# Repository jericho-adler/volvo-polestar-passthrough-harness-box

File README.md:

# Volvo/Polestar Passthrough Harness Box

# 🚧 IN DEVELOPMENT 🚧

> [!WARNING]
> **This branch (`flexray-integration`) is work in progress and has not been built or tested in a vehicle.**
> The FlexRay schematic is complete and ERC-clean, and the PCB is fully routed and DRC-clean, but no board
> has been fabricated or bench-tested yet. The `main` branch holds the last stable design.

A small automotive ADAS harness pass-through box designed in KiCad, built for **Volvo/Polestar** vehicles. It sits inline on the camera/VCU harness and provides a fail-safe electrical bypass plus signal switching, protected against automotive power-rail transients and ESD.
- **Board:** 98.0 × 58.0 mm, 4-layer (F.Cu / In1.Cu=GND / In2.Cu / B.Cu), 80 components, 126 nets.
  Corners are radiused 3.8 mm, concentric with the four M3 mounting holes
- **Power inputs:** VBAT and VOBD, each TVS-protected (SMAJ16A) and OR'd through Schottky diodes (STPS2H100ZFY) into a combined VIN rail
- **Fail-safe passthrough:** a DPDT relay (Omron G5V-2-H1 DC12) wired so the normally-closed contacts connect CAMERA↔VCU when the box is unpowered, and open when VIN is applied. The coil sits directly across VIN/GND, so the high-sensitivity `-H1` variant is used: 150 mW instead of 500 mW, and a 180% max coil voltage (21.6 V) that tolerates a running alternator rail
- **Signal switching:** two DG419 SPDT analog switches route CAMERA/VCU signal pairs under control of an `SBU 1` logic input
- **Protection:** PESD1CAN ESD diodes on signal lines at the connectors
- **Connectors:** JAE MX34032NF4 (32-pin automotive, ×2) for the harness pass-through, plus a USB-C and Molex connector

## FlexRay MITM (this branch)

This branch adds a **man-in-the-middle tap on the vehicle's FlexRay bus** (harness pins 29 & 30) to the
existing pass-through box, so the bus can be observed and rewritten in transit rather than merely bridged.

The FlexRay pair no longer runs straight from `J4` (car harness) to `J3` (VCU module). It is cut into two
independent halves — `FR_VEH_P`/`FR_VEH_N` on `J4` and `FR_ECU_P`/`FR_ECU_N` on `J3` — each terminated in
its own transceiver, with the microcontroller between them relaying frames.

- **Controller:** Seeed **XIAO RP2350** module (`U4`), running [dynm/pico-flexray](https://github.com/dynm/pico-flexray)
- **Transceivers:** two **NXP TJA1082** (`U5` VCU module side on `J3`, `U6` car harness side on `J4`), one per bus half. Logic pins run
  to the XIAO as `FR1_*`/`FR2_*` (RXD/TXD/TXEN) with shared `FR_BGE` and `FR_STBN`; `VCC` on +5 V, `VIO` on
  +3.3 V so the module's own LDO sets the logic level
- **Fail-safe bypass:** a second DPDT relay `K2` (Omron G5V-2-H1 DC12) whose **normally-closed** contacts bridge
  the two halves back together. De-energized — unpowered box, crashed firmware, or the XIAO simply not driving
  it — the vehicle and ECU are wired directly to each other and the bus behaves as if the box were not there.
  Energizing it **splits** the bus into the MITM path. Driven from the XIAO via `FR_BYPASS_CTRL` → `Q2`
  (DMN3200U) with a 1N4148 flyback diode
- **Power:** `U3` **LM53601-Q1** buck (12 V → 5 V, always-on, forced PWM) with a 4.7 µH Coilcraft XAL4030
  inductor, feeding the XIAO's 5 V input; the XIAO's 3V3 regulator in turn supplies transceiver `VIO`
- **Protection:** PESD1FLEX ESD diodes (`D10`, `D11`) on each bus half at its connector

The original harness board — relay `K1` plus the two DG419 analog switches — is
**unchanged** and operates independently of the FlexRay circuit.

### Mechanical and DRC notes

- **Outline:** 98.0 × 58.0 mm. The four corners are arcs of **R3.8 mm** whose centres sit exactly on the
  mounting-hole centres, so each corner is concentric with its hole.
- **Mounting:** 4 × M3 holes, 3.2 mm drill, **non-plated**, inset 3.8 mm from both edges (`H1`–`H4`).
  They are deliberately non-plated so the enclosure screws do not bond chassis to board ground — harness
  pin 13 is not board GND. They exist on the PCB only, with no schematic symbols, so do not tick
  *delete footprints with no symbol* when running **Update PCB from Schematic**.
- **Edge-mounted connectors:** `J1`–`J4` overhang the board edge by design. `J3`/`J4` (JAE MX34032NF4)
  project 7.8 mm past the left and right edges respectively; their pads remain fully on the board.
- **Custom DRC rule** (`Polestar_Flexray.kicad_dru`): exempts intra-footprint pad spacing on `U3` and `U8`
  only. `U8`'s land pattern is based on TI drawing 4225320/A (RGY0020A), which places the exposed pad
  0.025 mm from every perimeter pin. On this board the 20 perimeter pads are **deliberately extended
  0.3 mm outward** beyond TI's pattern (extents about 3.9 × 4.9 mm instead of 3.3 × 4.3 mm), which opens that
  gap to 0.325 mm. The pads are non-solder-mask-defined, so bridging to the exposed pad is controlled by the
  stencil (78% paste coverage on pad 21) rather than by copper spacing. The rule is scoped to `U3`/`U8` so
  every other footprint is still checked normally.

### Status

| | |
|---|---|
| Schematic | Complete — 80 components, 0 ERC errors |
| Footprints & 3D models | All 80 components assigned and resolving |
| Placement | Complete — 84 footprints (80 components + 4 mounting holes) on a 98 × 58 mm outline |
| Routing | **Complete** — 1370 track segments, 224 vias, 0 unrouted. In1.Cu is a solid GND pour; In2.Cu is a +5V plane with a VIN island under the input and buck section; all pours filled |
| DRC | 0 errors, 0 unconnected, 0 silkscreen warnings. The only warnings left are 12 footprints that differ from `Library/` (board-local silkscreen trims) and 4 schematic-parity notes for the `H1`–`H4` mounting holes, which have no symbols |
| Firmware | In Progress with Dev Board |
| Bench / vehicle testing | In Progress with Dev Board |

### Libraries

Custom symbols and footprints live in [`Library/`](Library/), and [`PCB Files/`](PCB%20Files/) carries
project-local `fp-lib-table` and `sym-lib-table` pointing at them through `${KIPRJMOD}`. The project
therefore opens on a fresh clone without editing any global KiCad library table.

| | |
|---|---|
| `Library/Symbols/` | 6 symbol libraries — 17 custom symbols, all resolving |
| `Library/Footprints.pretty/` | 91 footprints — the 33 used by this design all resolve |

Everything else comes from stock KiCad libraries (`Device`, `power`, `Crystal`, `Inductor_SMD`,
`Package_SO`, `Package_SON`, `MountingHole`).

> [!NOTE]
> **3D models are not included.** 44 of the model references point at a personal model directory
> (`${KICAD_USER_3D_MODELS}`, 14 distinct files — the XIAO, both JAE connectors, Molex, TJA1082,
> DG419, TCAN4550 and others). Those parts will render as bare pads in the 3D viewer on a clone.
> The design, netlist, footprints and fabrication outputs are unaffected. The remaining 36 model
> references resolve from stock KiCad.

Project files live in [`PCB Files/`](PCB%20Files/) as `Polestar_Flexray.kicad_{pro,sch,pcb,dru}`.

> [!IMPORTANT]
> `Polestar_Flexray.kicad_dru` carries a custom DRC rule and should be kept beside the project files.
> The current board passes DRC without it, but restoring `U8` to TI's exact land pattern would bring back
> 20 false clearance errors. See **Mechanical and DRC notes** above.

## License

Licensed under the [CERN Open Hardware Licence Version 2 - Strongly Reciprocal](LICENSE) (CERN-OHL-S-2.0).

## Disclaimer

This is a community hardware design shared as-is, with no warranty. It is designed specifically for Volvo/Polestar vehicles — using it on other platforms is unverified. **Use at your own risk.** Review the design review's blockers before fabricating or installing in a vehicle.

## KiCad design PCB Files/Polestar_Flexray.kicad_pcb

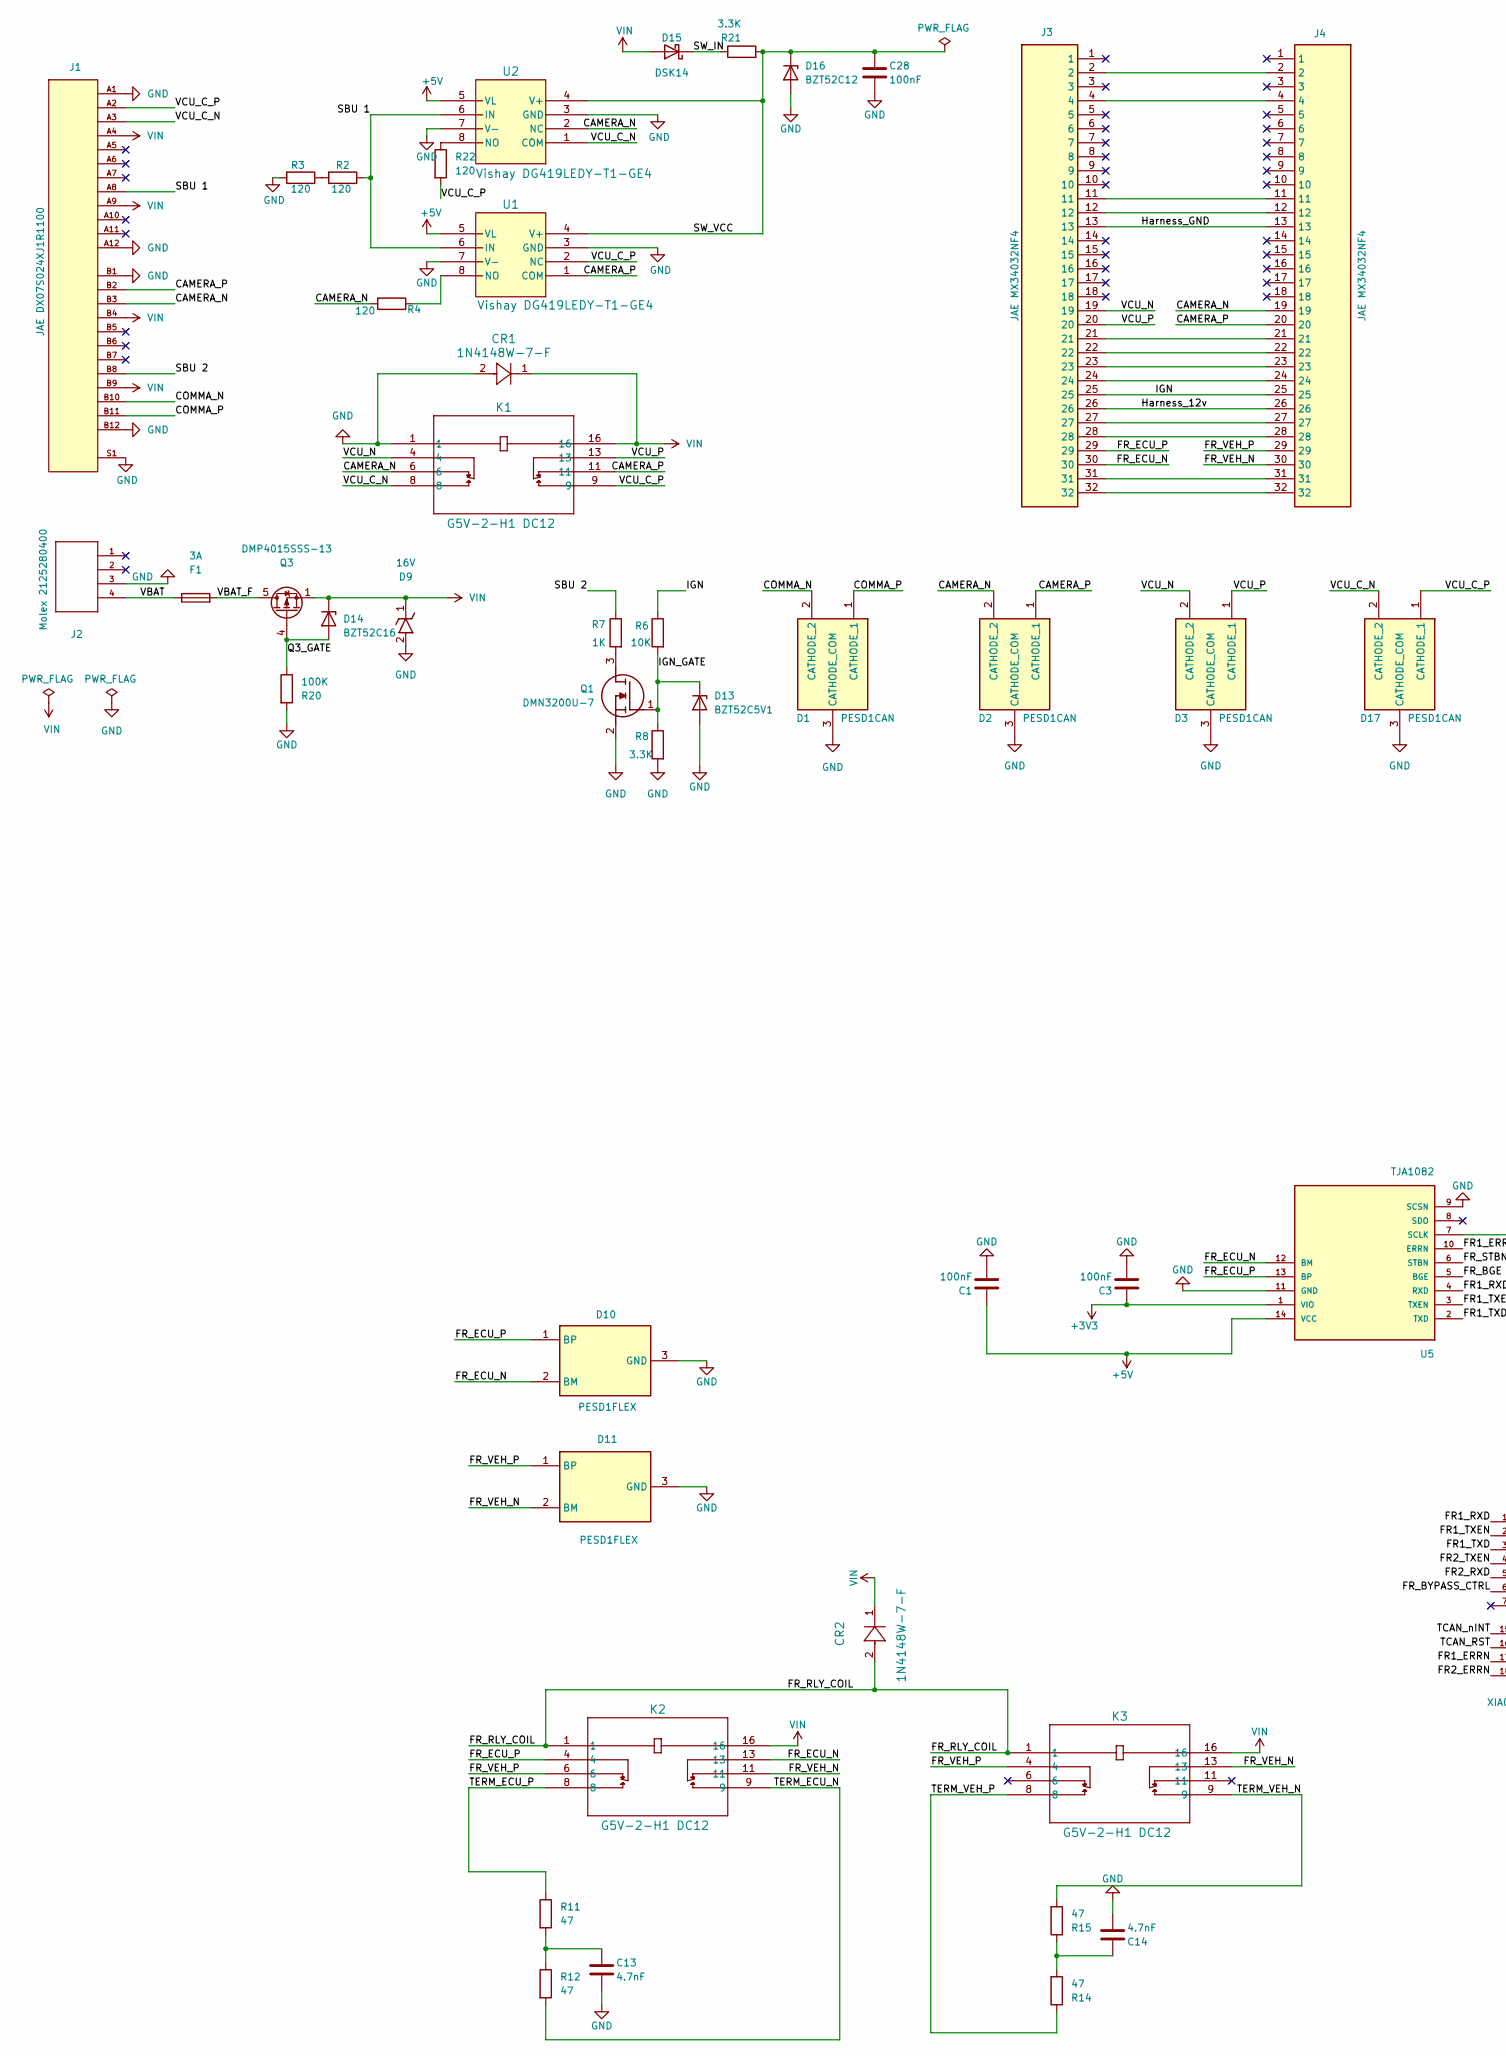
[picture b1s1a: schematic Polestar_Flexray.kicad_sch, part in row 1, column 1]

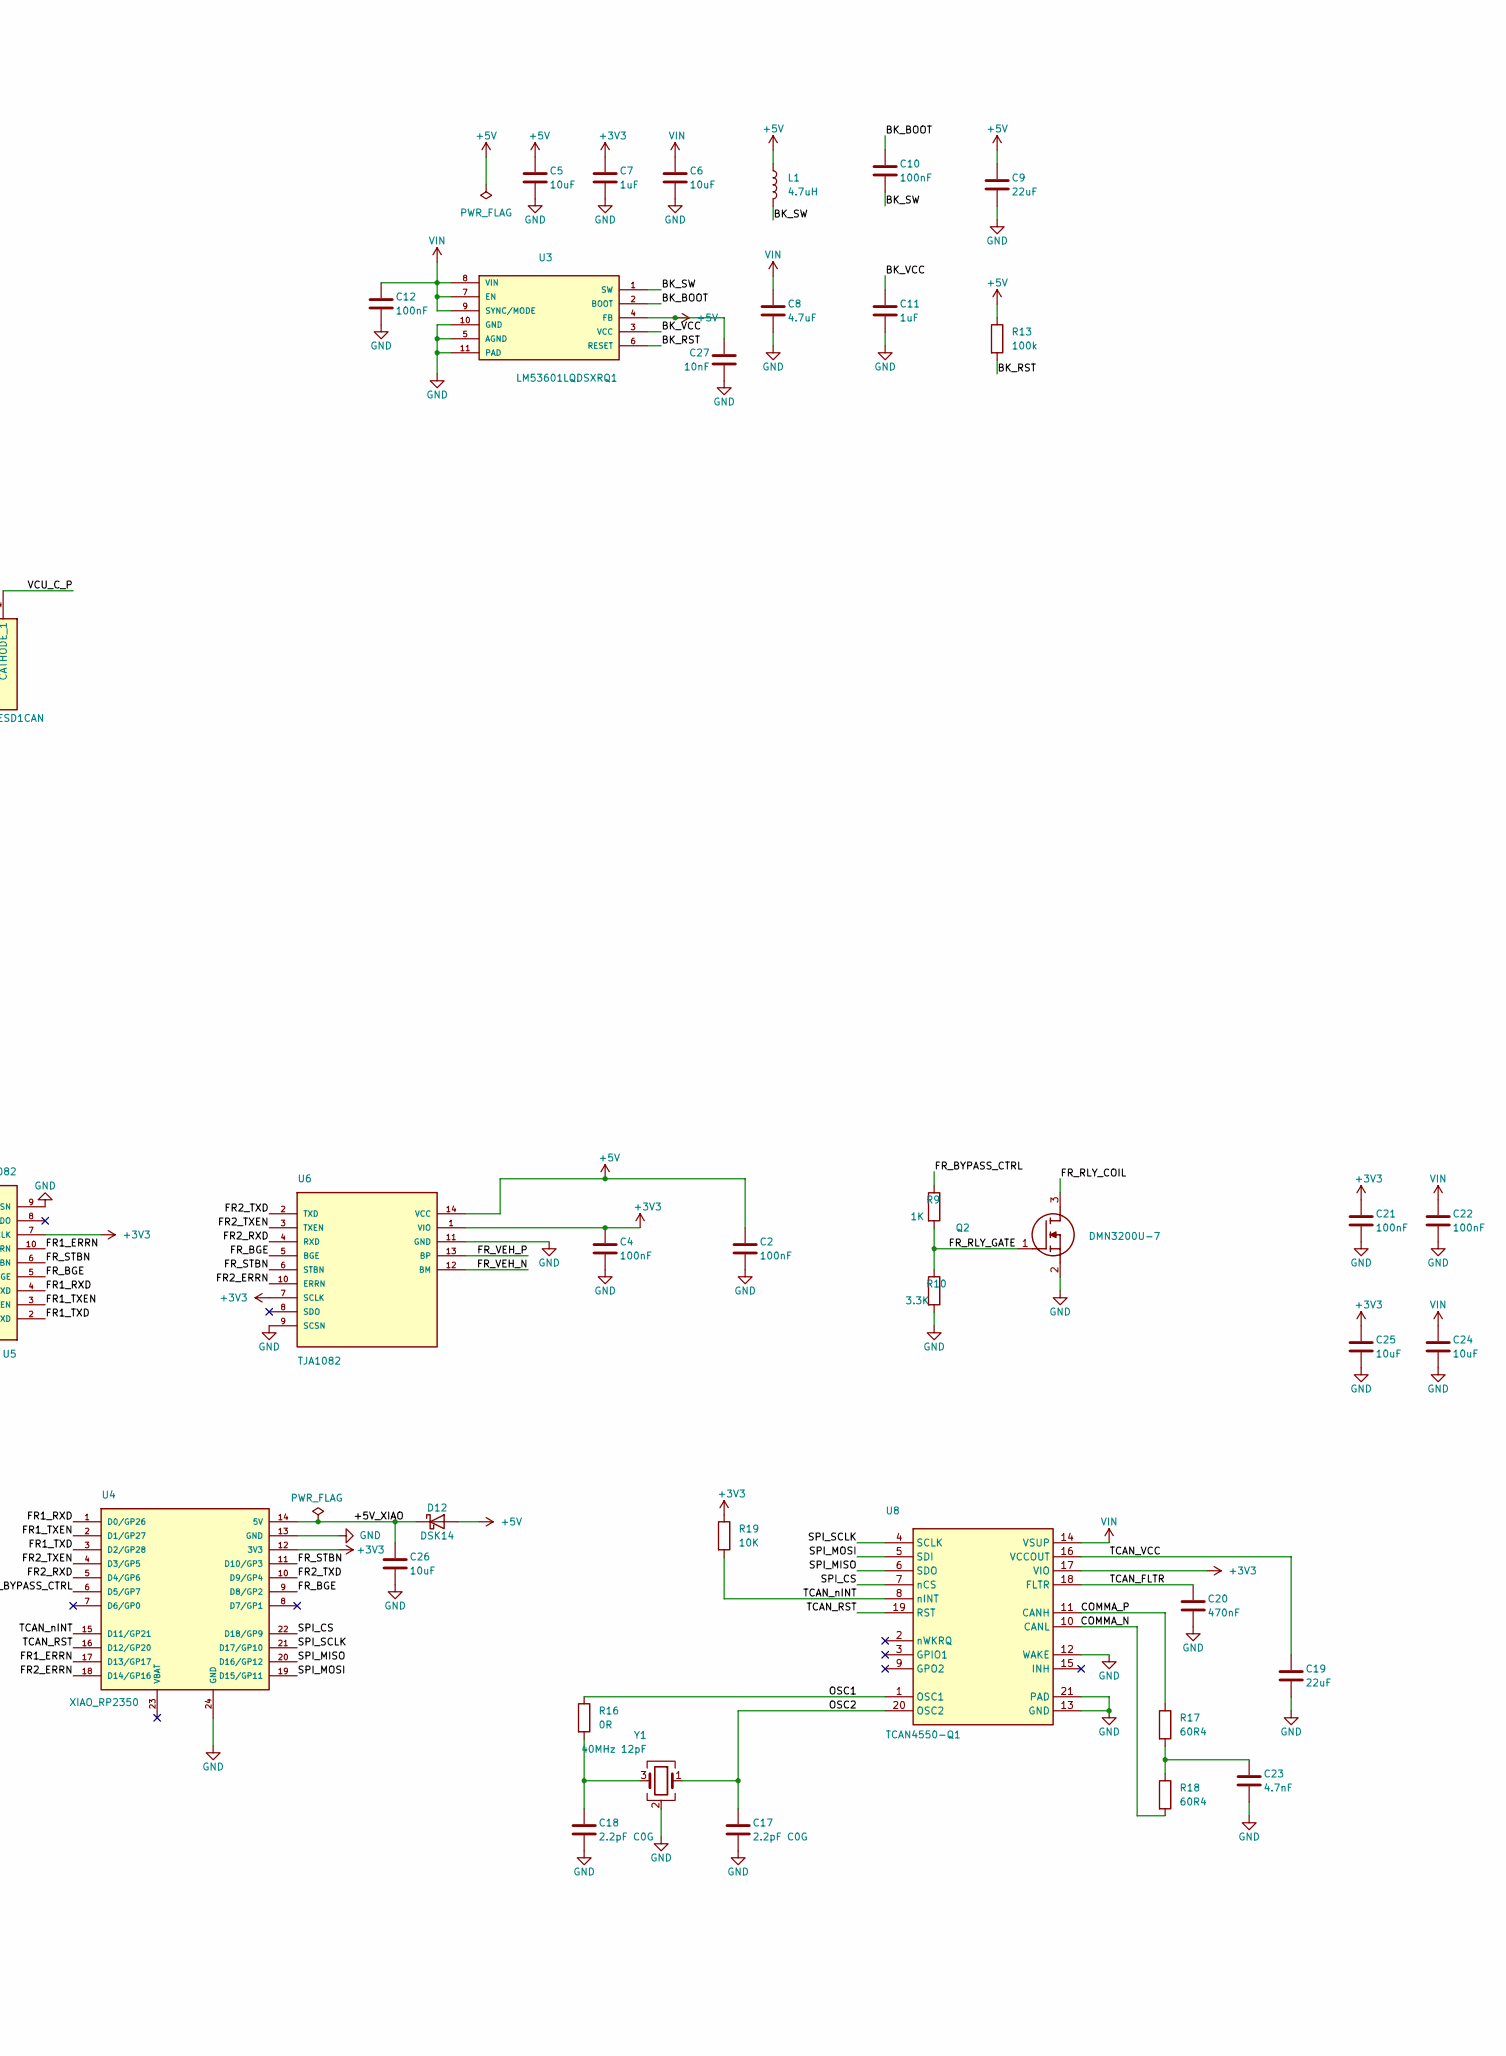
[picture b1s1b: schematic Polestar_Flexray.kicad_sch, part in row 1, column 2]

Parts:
C1, C2, C3, C4, C10, C12, C21, C22, C28: 100nF; SAMS CL10B104KB8NNNC; MFG Part # CL10B104KB8NNN; JLCPCB Part # C1591
C5, C25, C26: 10uF; SAMS CL21B106KAYQNNE; MFG Part # CL21B106KAYQNNE; JLCPCB Part # C3039694
C6, C24: 10uF; Taiyo UMK325AB7106KM-P; MFG Part # UMK325AB7106KM-P; JLCPCB Part # C337485
C7, C11: 1uF; SAMS CL10B105KA8NNNC; MFG Part # CL10B105KA8NNN; JLCPCB Part # C29936
C8: 4.7uF; SAMS CL31B475KBHNNNE; MFG Part # CL31B475KBHNNNE; JLCPCB Part # C51205
C9, C19: 22uF; SAMS CL32B226KAJNNNE; MFG Part # CL32B226KAJNNNE; JLCPCB Part # C309062
C13, C14, C23: 4.7nF; SAMS CL10B472KB8NNNC; MFG Part # CL10B472KB8NNNC; JLCPCB Part # C1621
C17, C18: 2.2pF C0G; FH 0603CG2R2C500NT; MFG Part # 0603CG2R2C500NT; JLCPCB Part # C1651
C20: 470nF; SAMS CL10B474KA8NNNC; MFG Part # CL10B474KA8NNNC; JLCPCB Part # C1623
C27: 10nF; SAMS CL05B103KA5NNNC; MFG Part # CL05B103KA5NNNC; JLCPCB Part # C318576
CR1, CR2: 1N4148W-7-F; SOD123_DIO; MFG Part # 1N4148W-7-F; JLCPCB Part # C83528
D1, D2, D3, D17: PESD1CAN; MFG Part # PESD1CAN,215; JLCPCB Part # C15771
D9: 16V; SMAJ16A; MFG Part # SMAJ16A; JLCPCB Part # C74561
D10, D11: PESD1FLEX; MFG Part # PESD1FLEX; JLCPCB Part # C2905640
D12, D15: DSK14; SCHOTTKY - 1A; MFG Part # DSK14; JLCPCB Part # C908228
D13: BZT52C5V1; SOD123_DIO; MFG Part # BZT52C5V1-7-F; JLCPCB Part # C151588
D14: BZT52C16; SOD123_DIO; MFG Part # BZT52C16-7-F; JLCPCB Part # C397929
D16: BZT52C12; SOD123_DIO; MFG Part # BZT52C12-7-F; JLCPCB Part # C124196
F1: 3A; Walter Elec 1206T3A63V; MFG Part # 1206T3A63V; JLCPCB Part # C354897
J1: JAE DX07S024XJ1R1100; MFG Part # DX07S024XJ1R1100; JLCPCB Part # C134113
J2: Molex 2125280400; MFG Part # 212528-0400; JLCPCB Part # C5354889
J3, J4: JAE MX34032NF4; MFG Part # MX34032NF4; JLCPCB Part # C5359473
K1, K2, K3: G5V-2-H1 DC12; Omron G5V-2-H1-DC12; MFG Part # G5V-2-H1 DC12; JLCPCB Part # C128021
L1: 4.7uH; L_Coilcraft_XAL4030-XXX; MFG Part # XAL4030-472MEC; JLCPCB Part # C19191688
Q1, Q2: DMN3200U-7; MFG Part # DMN3200U-7; JLCPCB Part # C461018
Q3: DMP4015SSS-13; SOIC-8_3.9x4.9mm_P1.27mm; MFG Part # DMP4015SSS-13; JLCPCB Part # C508210
R2, R3, R4, R22: 120; Rohm ESR03EZPJ121; MFG Part # ESR03EZPJ121; JLCPCB Part # C2846664
R6, R19: 10K; Rohm ESR03EZPJ103; MFG Part # ESR03EZPJ103; JLCPCB Part # C253330
R7, R9: 1K; Rohm ESR03EZPJ102; MFG Part # ESR03EZPJ102; JLCPCB Part # C253329
R8, R10, R21: 3.3K; Rohm ESR03EZPJ332; MFG Part # ESR03EZPF3301; JLCPCB Part # C510091
R11, R12, R14, R15: 47; Rohm ESR03EZPJ470; MFG Part # ESR03EZPJ470; JLCPCB Part # C5290207
R13: 100k; Rohm ESR03EZPJ104; MFG Part # ESR03EZPJ104; JLCPCB Part # C253331
R16: 0R; R_0603_1608Metric; MFG Part # 0603WAF0000T5E; JLCPCB Part # C21189
R17, R18: 60R4; YAGEO AC0603FR-7W60R4L; MFG Part # AC0603FR-7W60R4L; JLCPCB Part # C20142038
R20: 100K; Rohm ESR03EZPJ104; MFG Part # ESR03EZPJ104; JLCPCB Part # C253331
U1, U2: Vishay DG419LEDY-T1-GE4; MFG Part # DG419LEDY-T1-GE4; JLCPCB Part # C2673265
U3: LM53601LQDSXRQ1; TI LM53601LQDSXRQ1; MFG Part # LM53601LQDSXRQ1; JLCPCB Part # C2073079
U4: XIAO_RP2350; XIAO-RP2350-SMD; MFG Part # 102010550; JLCPCB Part # C41882923
U5, U6: TJA1082; NXP TJA1082; MFG Part # TJA1082TT,118; JLCPCB Part # C2674434
U8: TCAN4550-Q1; TI TCAN4550RGYRQ1; MFG Part # TCAN4550RGYTQ1; JLCPCB Part # C5215852
Y1: 40MHz 12pF; Crystal_SMD_2016-4Pin_2.0x1.6mm; MFG Part # SL201640M12P; JLCPCB Part # C5155517

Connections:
+3V3: C3.1, C4.1, C7.1, C21.1, C25.1, R19.1, U4.12 (3V3), U5.1 (VIO), U5.7 (SCLK), U6.1 (VIO), U6.7 (SCLK), U8.17 (VIO)
+5V: C1.1, C2.1, C5.1, C9.1, C27.1, D12.2 (A), L1.1, R13.1, U1.5 (VL), U2.5 (VL), U3.4 (FB), U5.14 (VCC), U6.14 (VCC)
/+5V_XIAO: C26.1, D12.1 (K), U4.14 (5V)
/BK_BOOT: C10.1, U3.2 (BOOT)
/BK_RST: R13.2, U3.6 (RESET)
/BK_SW: C10.2, L1.2, U3.1 (SW)
/BK_VCC: C11.1, U3.3 (VCC)
/CAMERA_N: D2.2 (CATHODE_2), J1.B3, J4.19, K1.6, R4.2, U2.2 (NC)
/CAMERA_P: D2.1 (CATHODE_1), J1.B2, J4.20, K1.11, U1.1 (COM)
/COMMA_N: D1.2 (CATHODE_2), J1.B10, R18.2, U8.10 (CANL)
/COMMA_P: D1.1 (CATHODE_1), J1.B11, R17.1, U8.11 (CANH)
/FR1_ERRN: U4.17 (D13/GP17), U5.10 (ERRN)
/FR1_RXD: U4.1 (D0/GP26), U5.4 (RXD)
/FR1_TXD: U4.3 (D2/GP28), U5.2 (TXD)
/FR1_TXEN: U4.2 (D1/GP27), U5.3 (TXEN)
/FR2_ERRN: U4.18 (D14/GP16), U6.10 (ERRN)
/FR2_RXD: U4.5 (D4/GP6), U6.4 (RXD)
/FR2_TXD: U4.10 (D9/GP4), U6.2 (TXD)
/FR2_TXEN: U4.4 (D3/GP5), U6.3 (TXEN)
/FR_BGE: U4.9 (D8/GP2), U5.5 (BGE), U6.5 (BGE)
/FR_BYPASS_CTRL: R9.1, U4.6 (D5/GP7)
/FR_ECU_N: D10.2 (BM), J3.30, K2.13, U5.12 (BM)
/FR_ECU_P: D10.1 (BP), J3.29, K2.4, U5.13 (BP)
/FR_RLY_COIL: CR2.2, K2.1, K3.1, Q2.3 (D)
/FR_RLY_GATE: Q2.1 (G), R9.2, R10.1
/FR_STBN: U4.11 (D10/GP3), U5.6 (STBN), U6.6 (STBN)
/FR_VEH_N: D11.2 (BM), J4.30, K2.11, K3.13, U6.12 (BM)
/FR_VEH_P: D11.1 (BP), J4.29, K2.6, K3.4, U6.13 (BP)
/Harness_12v: J3.26, J4.26
/Harness_GND: J3.13, J4.13
/IGN: J3.25, J4.25, R6.1
/IGN_GATE: D13.1 (K), Q1.1 (G), R6.2, R8.1
/OSC1: R16.1, U8.1 (OSC1)
/OSC2: C17.1, U8.20 (OSC2), Y1.1
/Q3_GATE: D14.2 (A), Q3.4 (G), R20.1
/SBU 1: J1.A8, R2.1, U1.6 (IN), U2.6 (IN)
/SBU 2: J1.B8, R7.1
/SPI_CS: U4.22 (D18/GP9), U8.7 (nCS)
/SPI_MISO: U4.20 (D16/GP12), U8.6 (SDO)
/SPI_MOSI: U4.19 (D15/GP11), U8.5 (SDI)
/SPI_SCLK: U4.21 (D17/GP10), U8.4 (SCLK)
/SW_IN: D15.1 (K), R21.1
/SW_VCC: C28.1, D16.1 (K), R21.2, U1.4 (V+), U2.4 (V+)
/TCAN_FLTR: C20.1, U8.18 (FLTR)
/TCAN_RST: U4.16 (D12/GP20), U8.19 (RST)
/TCAN_VCC: C19.1, U8.16 (VCCOUT)
/TCAN_nINT: R19.2, U4.15 (D11/GP21), U8.8 (nINT)
/TERM_ECU_N: K2.9, R12.2
/TERM_ECU_P: K2.8, R11.1
/TERM_VEH_N: K3.9, R15.2
/TERM_VEH_P: K3.8, R14.1
/VBAT: F1.1, J2.4
/VBAT_F: F1.2, Q3.5 (D), Q3.6 (D), Q3.7 (D), Q3.8 (D)
/VCU_C_N: D17.2 (CATHODE_2), J1.A3, K1.8, U2.1 (COM)
/VCU_C_P: D17.1 (CATHODE_1), J1.A2, K1.9, R22.2, U1.2 (NC)
/VCU_N: D3.2 (CATHODE_2), J3.19, K1.4
/VCU_P: D3.1 (CATHODE_1), J3.20, K1.13
GND: C1.2, C2.2, C3.2, C4.2, C5.2, C6.2, C7.2, C8.2, C9.2, C11.2, C12.2, C13.2, C14.2, C17.2, C18.2, C19.2, C20.2, C21.2, C22.2, C23.2, C24.2, C25.2, C26.2, C27.2, C28.2, CR1.2, D1.3 (CATHODE_COM), D2.3 (CATHODE_COM), D3.3 (CATHODE_COM), D9.2, D10.3 (GND), D11.3 (GND), D13.2 (A), D16.2 (A), D17.3 (CATHODE_COM), J1.A1, J1.A12, J1.B1, J1.B12, J1.S1, J2.3, K1.1, Q1.2 (S), Q2.2 (S), R3.2, R8.2, R10.2, R20.2, U1.3 (GND), U1.7 (V-), U2.3 (GND), U2.7 (V-), U3.5 (AGND), U3.10 (GND), U3.11 (PAD), U4.13 (GND), U4.24 (GND), U5.9 (SCSN), U5.11 (GND), U6.9 (SCSN), U6.11 (GND), U8.12 (WAKE), U8.13 (GND), U8.21 (PAD), Y1.2 (G), Y1.4 (G)
unnamed: C13.1, R11.2, R12.1
unnamed: C14.1, R14.2, R15.1
unnamed: C18.1, R16.2, Y1.3
unnamed: C23.1, R17.2, R18.1
unnamed: J3.2, J4.2
unnamed: J3.4, J4.4
unnamed: J3.11, J4.11
unnamed: J3.12, J4.12
unnamed: J3.21, J4.21
unnamed: J3.22, J4.22
unnamed: J3.23, J4.23
unnamed: J3.24, J4.24
unnamed: J3.27, J4.27
unnamed: J3.28, J4.28
unnamed: J3.31, J4.31
unnamed: J3.32, J4.32
unnamed: Q1.3 (D), R7.2
unnamed: R2.2, R3.1
unnamed: R4.1, U1.8 (NO)
unnamed: R22.1, U2.8 (NO)
VIN: C6.1, C8.1, C12.1, C22.1, C24.1, CR1.1, CR2.1, D9.1, D14.1 (K), D15.2 (A), J1.A4, J1.A9, J1.B4, J1.B9, K1.16, K2.16, K3.16, Q3.1 (S), Q3.2 (S), Q3.3 (S), U3.7 (EN), U3.8 (VIN), U3.9 (SYNC/MODE), U8.14 (VSUP)

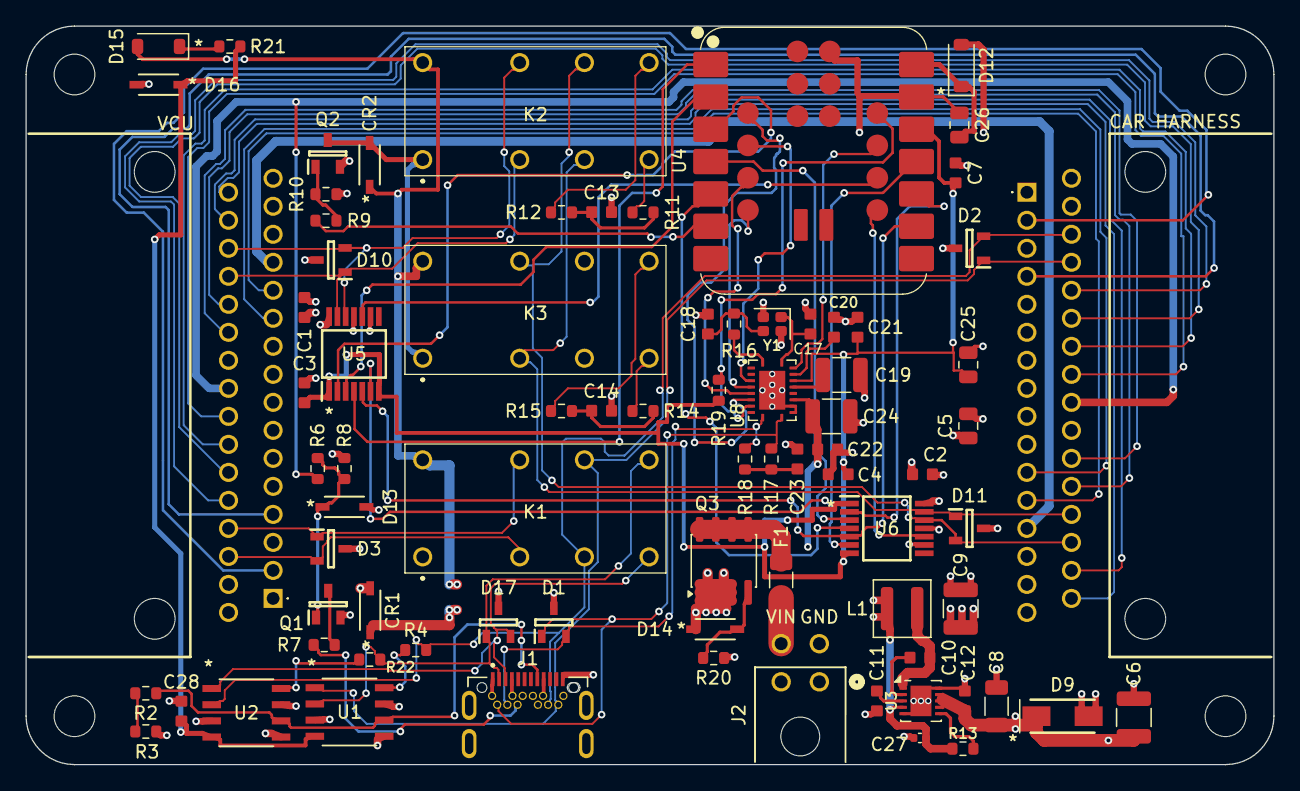
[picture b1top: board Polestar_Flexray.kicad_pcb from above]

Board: 4 copper layers, 98.0 x 58.0 mm, 84 parts (0 on the bottom side), 79 nets.

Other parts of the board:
H1, H2, H3, H4: MountingHole_3.2mm_M3

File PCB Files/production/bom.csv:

Designator,Footprint,Quantity,Value,LCSC Part #
"C1, C10, C12, C2, C21, C22, C28, C3, C4",SAMS CL10B104KB8NNNC,9,100nF,C1591
"C11, C7",SAMS CL10B105KA8NNNC,2,1uF,C29936
"C13, C14, C23",SAMS CL10B472KB8NNNC,3,4.7nF,C1621
"C17, C18",FH 0603CG2R2C500NT,2,2.2pF C0G,C1651
"C19, C9",SAMS CL32B226KAJNNNE,2,22uF,C309062
C20,SAMS CL10B474KA8NNNC,1,470nF,C1623
"C24, C6",Taiyo UMK325AB7106KM-P,2,10uF,C337485
"C25, C26, C5",SAMS CL21B106KAYQNNE,3,10uF,C3039694
C27,SAMS CL05B103KA5NNNC,1,10nF,C318576
C8,SAMS CL31B475KBHNNNE,1,4.7uF,C51205
"CR1, CR2",SOD123_DIO,2,1N4148W-7-F,C83528
"D1, D17, D2, D3",PESD1CAN,4,PESD1CAN,C15771
"D10, D11",PESD1FLEX,2,PESD1FLEX,C2905640
"D12, D15",SCHOTTKY - 1A,2,DSK14,C908228
D13,SOD123_DIO,1,BZT52C5V1,C151588
D14,SOD123_DIO,1,BZT52C16,C397929
D16,SOD123_DIO,1,BZT52C12,C124196
D9,SMAJ16A,1,16V,C74561
F1,Walter Elec 1206T3A63V,1,3A,C354897
J1,JAE DX07S024XJ1R1100,1,JAE DX07S024XJ1R1100,C134113
J2,Molex 2125280400,1,Molex 2125280400,C5354889
"J3, J4",JAE MX34032NF4,2,JAE MX34032NF4,C5359473
"K1, K2, K3",Omron G5V-2-H1-DC12,3,G5V-2-H1 DC12,C128021
L1,L_Coilcraft_XAL4030-XXX,1,4.7uH,C19191688
"Q1, Q2",DMN3200U-7,2,DMN3200U-7,C461018
Q3,SOIC-8_3.9x4.9mm_P1.27mm,1,DMP4015SSS-13,C508210
"R10, R21, R8",Rohm ESR03EZPJ332,3,3.3K,C510091
"R11, R12, R14, R15",Rohm ESR03EZPJ470,4,47,C5290207
"R13, R20",Rohm ESR03EZPJ104,2,100k,C253331
R16,0603,1,0R,C21189
"R17, R18",YAGEO AC0603FR-7W60R4L,2,60R4,C20142038
"R19, R6",Rohm ESR03EZPJ103,2,10K,C253330
"R2, R22, R3, R4",Rohm ESR03EZPJ121,4,120,C2846664
"R7, R9",Rohm ESR03EZPJ102,2,1K,C253329
"U1, U2",Vishay DG419LEDY-T1-GE4,2,Vishay DG419LEDY-T1-GE4,C2673265
U3,TI LM53601LQDSXRQ1,1,LM53601LQDSXRQ1,C2073079
U4,XIAO-RP2350-SMD,1,XIAO_RP2350,C41882923
"U5, U6",NXP TJA1082,2,TJA1082,C2674434
U8,TI TCAN4550RGYRQ1,1,TCAN4550-Q1,C5215852
Y1,Crystal_SMD_2016-4Pin_2.0x1.6mm,1,40MHz 12pF,C5155517
